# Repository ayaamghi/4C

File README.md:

<div align="center">

# 4C

</div>

Four-channel brushed DC motor controller board built around an STM32G4, DRV8701 gate drivers, and discrete MOSFET bridges.

## Layout

- `hardware/kicad/4C.kicad_pro` - open this in KiCad
- `hardware/kicad/libs/` - project-local imported parts and 3D models
- `firmware/cubemx/` - STM32CubeMX config
- `docs/datasheets/` - datasheets and layout notes

Hardware is still in progress; check the schematic, BOM, and fab outputs before ordering.

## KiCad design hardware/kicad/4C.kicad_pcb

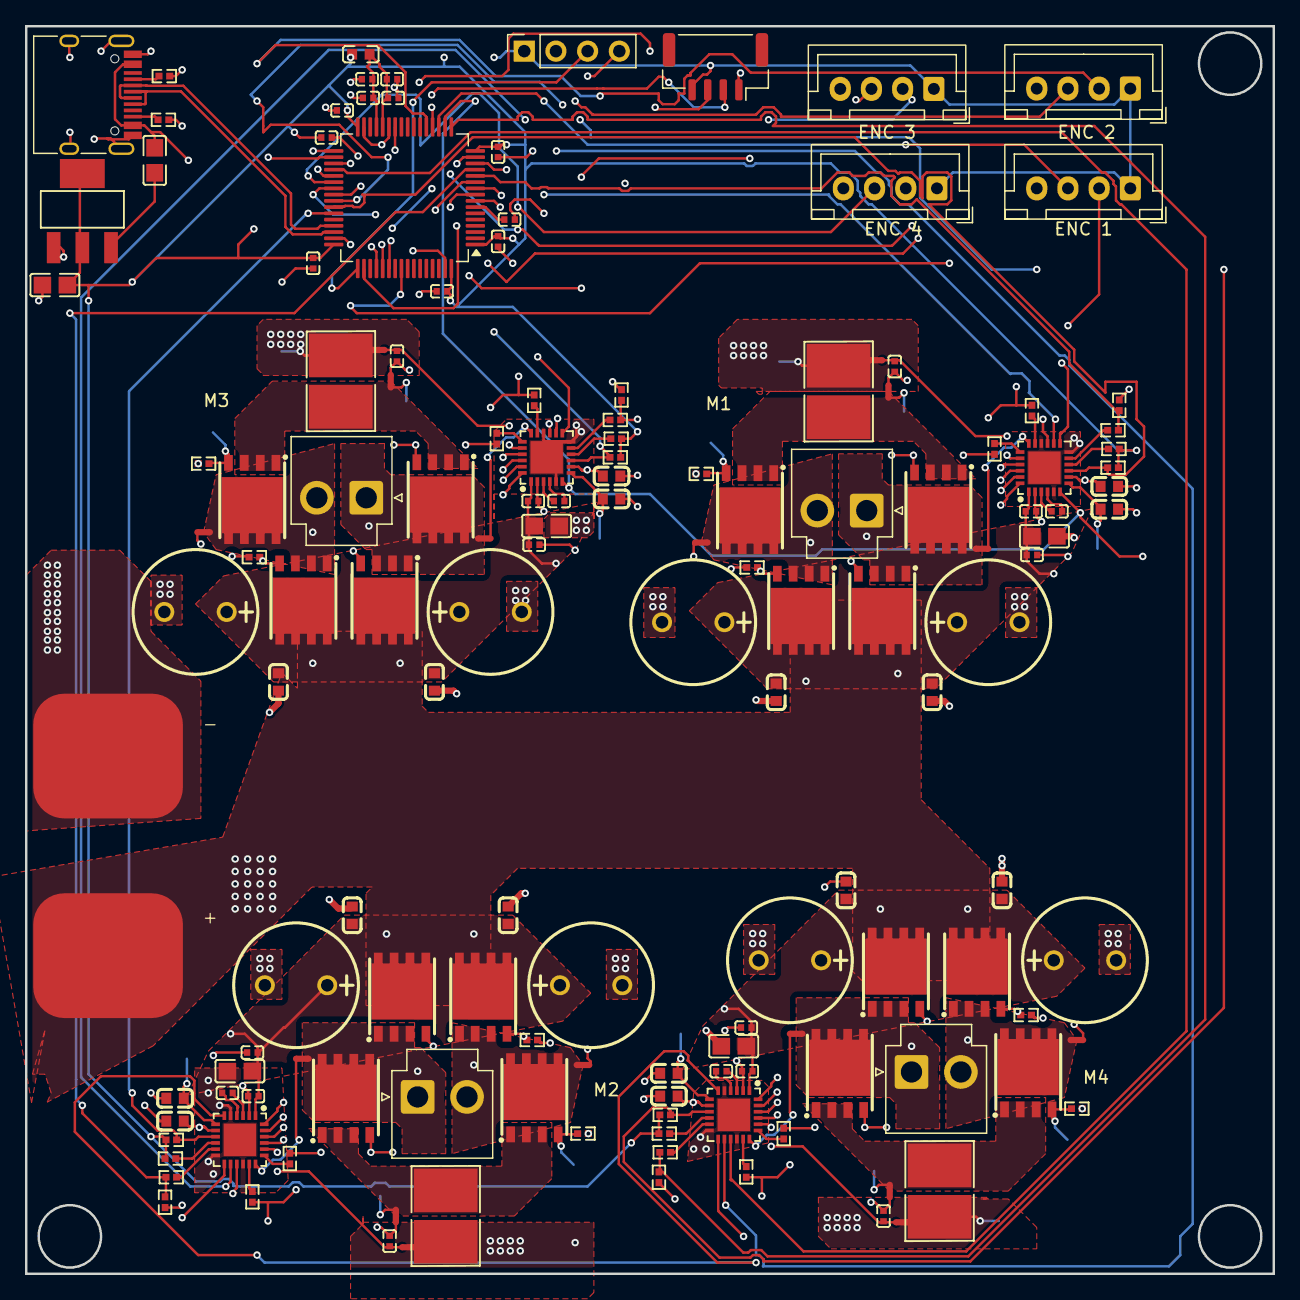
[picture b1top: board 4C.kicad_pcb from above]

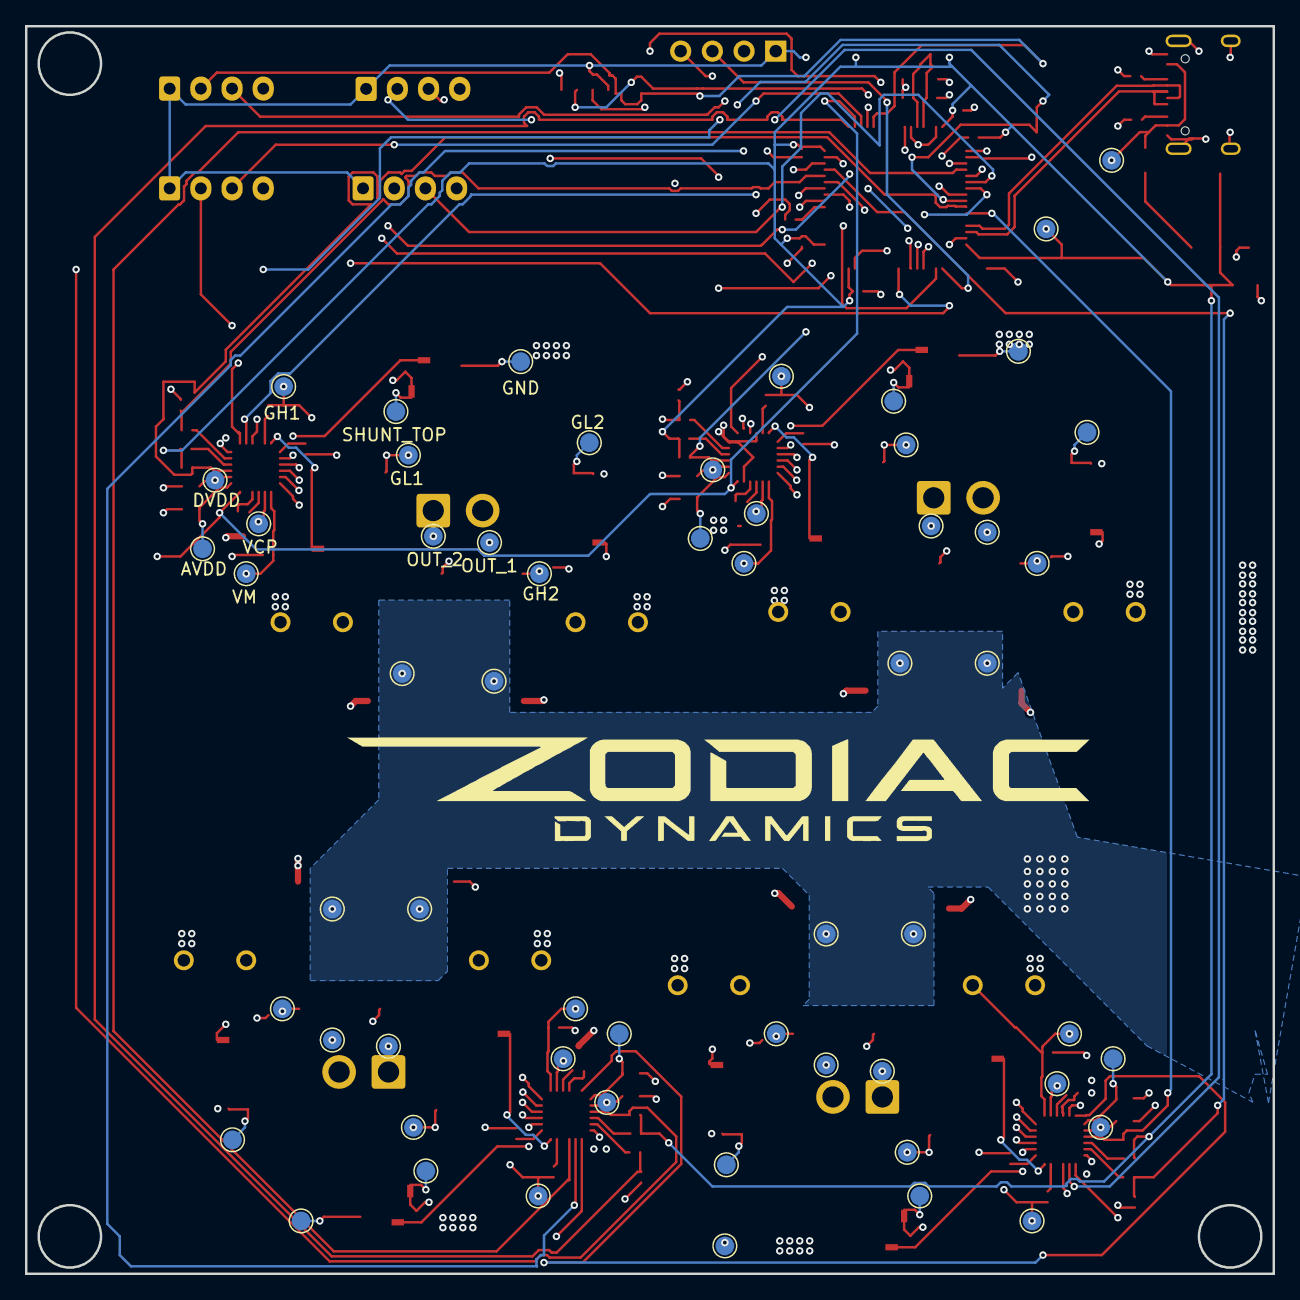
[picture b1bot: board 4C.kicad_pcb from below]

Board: 4 copper layers, 100.0 x 100.0 mm, 204 parts (58 on the bottom side), 129 nets.

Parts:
C1, C16, C31, C46: GRM32ER71H106KA12L; C0805
C2, C6, C17, C21, C32, C36, C47, C51, C62, C64, C66, C67, C68, C69, C72, C73: C1608X7R1H104K; C0402
C3, C4, C7, C14, C18, C19, C22, C29, C33, C34, C37, C44, C48, C49, C52, C59: GRM188R70J105KA01D; C0603
C5, C20, C35, C50, C61, C63: CL05A105KA5NQNC; C0402
C8, C15, C23, C30, C38, C45, C53, C60: ECA-1HM471; CAP-TH_BD10.0-P5.00-D0.6-FD
C9, C24, C39, C54: GRM155R71C102KA01D; C0402
C65: GRM32ER71H106KA12L; C0402
C70: 10uF; C0805
C71: 22uF; C0805
J1: Conn_01x04; PinSocket_1x04_P2.54mm_Vertical
J2: Conn_01x02; SolderWirePad_2x01_SMD_10x12mm
J10, J11, J12, J13: Conn_01x02; JST_VH_B2P-VH_1x02_P3.96mm_Vertical
J18, J19, J20, J21: Conn_01x04; JST_XH_B4B-XH-A_1x04_P2.50mm_Vertical
J22: Conn_01x04; JST_GH_SM04B-GHS-TB_1x04-1MP_P1.25mm_Horizontal
J25: USB_C_Receptacle_USB2.0_16P; USB_C_Receptacle_HRO_TYPE-C-31-M-12
L1: GZ1608D601TF; L0603
NT1, NT2, NT3, NT4, NT5, NT6, NT7, NT8, NT9, NT10, NT11, NT12, NT13, NT14, NT15, NT16: Net-Tie; NetTie-2_SMD_Pad0.5mm
Q1, Q2, Q3, Q4, Q5, Q6, Q7, Q8, Q9, Q10, Q11, Q12, Q13, Q14, Q15, Q16: CSD18540Q5B; VSON-CLIP-8_L5.0-W6.0-P1.27-BL
R1, R2, R4, R12, R13, R15, R23, R24, R26, R34, R35, R37: CRCW060310K0JNEA; R0402
R3, R14, R25, R36: CRCW06037K50JNEA; R0402
R7, R8, R10, R11, R18, R19, R21, R22, R29, R30, R32, R33, R40, R41, R43, R44, R45, R46: CRCW06030000Z0EA; R0402
R9, R20, R31, R42: CRA2512-FZ-R010ELF; R2818
TP1, TP2, TP15, TP16, TP29, TP30, TP43, TP44: VM; TestPoint_Pad_D1.5mm
TP3, TP4, TP5, TP6, TP7, TP8, TP9, TP10, TP11, TP12, TP13, TP14, TP17, TP18, TP19, TP20, TP21, TP22, TP23, TP24, TP25, TP26, TP27, TP28, TP31, TP32, TP33, TP34, TP35, TP36, TP37, TP38, TP39, TP40, TP41, TP42, TP45, TP46, TP47, TP48, TP49, TP50, TP51, TP52, TP53, TP54, TP55, TP56: AVDD; TestPoint_Pad_D1.5mm
TP57, TP58: TestPoint; TestPoint_Pad_D1.5mm
U1, U2, U3, U4: DRV8701ERGER; VQFN-24_L4.0-W4.0-P0.50-BL-EP2.5
U5: STM32G474RETx; LQFP-64_10x10mm_P0.5mm
U6: AMS1117-3.3; SOT-223-3_L6.5-W3.4-P2.30-LS7.0-BR

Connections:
+3.3V: C65.1, C66.1, C67.1, C68.1, C69.1, C71.1, C73.1, J1.1, J18.1, J19.1, J20.1, J21.1, J22.4, L1.1, R1.1, R2.1, R12.1, R13.1, R23.1, R24.1, R34.1, R35.1, TP58.1, U5.1 (VBAT), U5.16 (VDD), U5.32 (VDD), U5.48 (VDD), U5.64 (VDD), U6.2 (VOUT), U6.4 (VOUT)
+5V: C70.2, J25.A4 (VBUS), J25.A9 (VBUS), J25.B4 (VBUS), J25.B9 (VBUS), TP57.1
/D+: J25.A6 (D+), J25.B6 (D+), U5.46 (PA12)
/D-: J25.A7 (D-), J25.B7 (D-), U5.45 (PA11)
/ENC_1_A: J18.3, U5.19 (PA5)
/ENC_1_B: J18.2, U5.56 (PB3)
/ENC_2_A: J19.3, U5.20 (PA6)
/ENC_2_B: J19.2, U5.21 (PA7)
/ENC_3_A: J20.3, U5.26 (PB2)
/ENC_3_B: J20.2, U5.54 (PC12)
/ENC_4_A: J21.3, U5.38 (PC6)
/ENC_4_B: J21.2, U5.39 (PC7)
/EN_1: U1.14 (EN/IN2), U5.8 (PC0)
/EN_2: U2.14 (EN/IN2), U5.9 (PC1)
/EN_3: U3.14 (EN/IN2), U5.10 (PC2)
/EN_4: U4.14 (EN/IN2), U5.11 (PC3)
/PH_DIR_1: U1.15 (PH/IN1), U5.33 (PB11)
/PH_DIR_2: U2.15 (PH/IN1), U5.34 (PB12)
/PH_DIR_3: U3.15 (PH/IN1), U5.35 (PB13)
/PH_DIR_4: U4.15 (PH/IN1), U5.36 (PB14)
/SO_1: R3.1, R4.1, U5.12 (PA0)
/SO_2: R14.1, R15.1, U5.13 (PA1)
/SO_3: R25.1, R26.1, U5.14 (PA2)
/SO_4: R36.1, R37.1, U5.17 (PA3)
/UART_RX: J22.2, U5.53 (PC11)
/UART_TX: J22.3, U5.52 (PC10)
/VREF: U1.6 (VREF), U2.6 (VREF), U3.6 (VREF), U4.6 (VREF), U5.18 (PA4)
/drh1/AVDD: C3.1, TP3.1, U1.7 (AVDD)
/drh1/DVDD: C4.2, TP4.1, U1.8 (DVDD)
/drh1/GH1: R10.1, U1.17 (GH1)
/drh1/GH2: R7.2, U1.24 (GH2)
/drh1/GL1: R11.1, U1.19 (GL1)
/drh1/GL2: R8.2, U1.22 (GL2)
/drh1/OUT1: J10.2, NT1.2, Q1.1 (S), Q1.2 (S), Q1.3 (S), Q2.5 (D), Q2.6 (D), Q2.7 (D), Q2.8 (D), TP8.1
/drh1/OUT2: J10.1, NT4.2, Q3.1 (S), Q3.2 (S), Q3.3 (S), Q4.5 (D), Q4.6 (D), Q4.7 (D), Q4.8 (D), TP10.1
/drh1/SH1: NT4.1, U1.18 (SH1)
/drh1/SH2: NT1.1, U1.23 (SH2)
/drh1/SHUNT_TOP: NT2.1, Q2.1 (S), Q2.2 (S), Q2.3 (S), Q4.1 (S), Q4.2 (S), Q4.3 (S), R9.2, TP9.1
/drh1/SNSOUT: R1.2, U1.10 (SNSOUT)
/drh1/S_N: C9.2, NT3.2, U1.20 (SN)
/drh1/S_P: C9.1, NT2.2, U1.21 (SP)
/drh1/VCP: C5.1, TP2.1, U1.2 (VCP)
/drh2/AVDD: C18.1, TP17.1, U2.7 (AVDD)
/drh2/DVDD: C19.2, TP18.1, U2.8 (DVDD)
/drh2/GH1: R21.1, U2.17 (GH1)
/drh2/GH2: R18.2, U2.24 (GH2)
/drh2/GL1: R22.1, U2.19 (GL1)
/drh2/GL2: R19.2, U2.22 (GL2)
/drh2/OUT1: J11.2, NT5.2, Q5.1 (S), Q5.2 (S), Q5.3 (S), Q6.5 (D), Q6.6 (D), Q6.7 (D), Q6.8 (D), TP22.1
/drh2/OUT2: J11.1, NT8.2, Q7.1 (S), Q7.2 (S), Q7.3 (S), Q8.5 (D), Q8.6 (D), Q8.7 (D), Q8.8 (D), TP24.1
/drh2/SH1: NT8.1, U2.18 (SH1)
/drh2/SH2: NT5.1, U2.23 (SH2)
/drh2/SHUNT_TOP: NT6.1, Q6.1 (S), Q6.2 (S), Q6.3 (S), Q8.1 (S), Q8.2 (S), Q8.3 (S), R20.2, TP23.1
/drh2/SNSOUT: R12.2, U2.10 (SNSOUT)
/drh2/S_N: C24.2, NT7.2, U2.20 (SN)
/drh2/S_P: C24.1, NT6.2, U2.21 (SP)
/drh2/VCP: C20.1, TP16.1, U2.2 (VCP)
/drh3/AVDD: C33.1, TP31.1, U3.7 (AVDD)
/drh3/DVDD: C34.2, TP32.1, U3.8 (DVDD)
/drh3/GH1: R32.1, U3.17 (GH1)
/drh3/GH2: R29.2, U3.24 (GH2)
/drh3/GL1: R33.1, U3.19 (GL1)
/drh3/GL2: R30.2, U3.22 (GL2)
/drh3/OUT1: J12.2, NT9.2, Q9.1 (S), Q9.2 (S), Q9.3 (S), Q10.5 (D), Q10.6 (D), Q10.7 (D), Q10.8 (D), TP36.1
/drh3/OUT2: J12.1, NT12.2, Q11.1 (S), Q11.2 (S), Q11.3 (S), Q12.5 (D), Q12.6 (D), Q12.7 (D), Q12.8 (D), TP38.1
/drh3/SH1: NT12.1, U3.18 (SH1)
/drh3/SH2: NT9.1, U3.23 (SH2)
/drh3/SHUNT_TOP: NT10.1, Q10.1 (S), Q10.2 (S), Q10.3 (S), Q12.1 (S), Q12.2 (S), Q12.3 (S), R31.2, TP37.1
/drh3/SNSOUT: R23.2, U3.10 (SNSOUT)
/drh3/S_N: C39.2, NT11.2, U3.20 (SN)
/drh3/S_P: C39.1, NT10.2, U3.21 (SP)
/drh3/VCP: C35.1, TP30.1, U3.2 (VCP)
/drh4/AVDD: C48.1, TP45.1, U4.7 (AVDD)
/drh4/DVDD: C49.2, TP46.1, U4.8 (DVDD)
/drh4/GH1: R43.1, U4.17 (GH1)
/drh4/GH2: R40.2, U4.24 (GH2)
/drh4/GL1: R44.1, U4.19 (GL1)
/drh4/GL2: R41.2, U4.22 (GL2)
/drh4/OUT1: J13.2, NT13.2, Q13.1 (S), Q13.2 (S), Q13.3 (S), Q14.5 (D), Q14.6 (D), Q14.7 (D), Q14.8 (D), TP50.1
/drh4/OUT2: J13.1, NT16.2, Q15.1 (S), Q15.2 (S), Q15.3 (S), Q16.5 (D), Q16.6 (D), Q16.7 (D), Q16.8 (D), TP52.1
/drh4/SH1: NT16.1, U4.18 (SH1)
/drh4/SH2: NT13.1, U4.23 (SH2)
/drh4/SHUNT_TOP: NT14.1, Q14.1 (S), Q14.2 (S), Q14.3 (S), Q16.1 (S), Q16.2 (S), Q16.3 (S), R42.2, TP51.1
/drh4/SNSOUT: R34.2, U4.10 (SNSOUT)
/drh4/S_N: C54.2, NT15.2, U4.20 (SN)
/drh4/S_P: C54.1, NT14.2, U4.21 (SP)
/drh4/VCP: C50.1, TP44.1, U4.2 (VCP)
/nFAULT_1: R2.2, U1.9 (FAULT), U5.42 (PA8)
/nFAULT_2: R13.2, U2.9 (FAULT), U5.43 (PA9)
/nFAULT_3: R24.2, U3.9 (FAULT), U5.40 (PC8)
/nFAULT_4: R35.2, U4.9 (FAULT), U5.41 (PC9)
/nSLEEP: U1.13 (SLEEP), U2.13 (SLEEP), U3.13 (SLEEP), U4.13 (SLEEP), U5.37 (PB15)
GND: C1.2, C2.2, C3.2, C4.1, C7.1, C8.2 (-), C14.1, C15.2 (-), C16.2, C17.2, C18.2, C19.1, C22.1, C23.2 (-), C29.1, C30.2 (-), C31.2, C32.2, C33.2, C34.1, C37.1, C38.2 (-), C44.1, C45.2 (-), C46.2, C47.2, C48.2, C49.1, C52.1, C53.2 (-), C59.1, C60.2 (-), C61.1, C62.2, C63.1, C64.2, C65.2, C66.2, C67.2, C68.2, C69.2, C71.2, C72.2, C73.2, J1.2, J2.1, J18.4, J19.4, J20.4, J21.4, J22.1, J25.A1 (GND), J25.A12 (GND), J25.B1 (GND), J25.B12 (GND), J25.S1 (SHIELD), NT3.1, NT7.1, NT11.1, NT15.1, R4.2, R9.1, R15.2, R20.1, R26.2, R31.1, R37.2, R42.1, R45.2, R46.2, TP11.1, TP25.1, TP39.1, TP53.1, U1.5 (GND), U1.12 (IDRIVE), U1.16 (GND), U1.25 (PAD), U2.5 (GND), U2.12 (IDRIVE), U2.16 (GND), U2.25 (PAD), U3.5 (GND), U3.12 (IDRIVE), U3.16 (GND), U3.25 (PAD), U4.5 (GND), U4.12 (IDRIVE), U4.16 (GND), U4.25 (PAD), U5.15 (VSS), U5.27 (VSSA), U5.31 (VSS), U5.47 (VSS), U5.63 (VSS), U6.1 (GND)
unnamed: J1.3, U5.49 (PA13)
unnamed: J1.4, U5.50 (PA14)
unnamed: J25.A5 (CC1), R45.1
unnamed: J25.B5 (CC2), R46.1
unnamed: Q1.4 (G), R7.1, TP5.1
unnamed: Q2.4 (G), R8.1, TP6.1
unnamed: Q3.4 (G), R10.2, TP13.1
unnamed: Q4.4 (G), R11.2, TP14.1
unnamed: Q5.4 (G), R18.1, TP19.1
unnamed: Q6.4 (G), R19.1, TP20.1
unnamed: Q7.4 (G), R21.2, TP27.1
unnamed: Q8.4 (G), R22.2, TP28.1
unnamed: Q9.4 (G), R29.1, TP33.1
unnamed: Q10.4 (G), R30.1, TP34.1
unnamed: Q11.4 (G), R32.2, TP41.1
unnamed: Q12.4 (G), R33.2, TP42.1
unnamed: Q13.4 (G), R40.1, TP47.1
unnamed: Q14.4 (G), R41.1, TP48.1
unnamed: Q15.4 (G), R43.2, TP55.1
unnamed: Q16.4 (G), R44.2, TP56.1
unnamed: C6.1, U1.3 (CPH)
unnamed: C6.2, U1.4 (CPL)
unnamed: R3.2, U1.11 (SO)
unnamed: C21.1, U2.3 (CPH)
unnamed: C21.2, U2.4 (CPL)
unnamed: R14.2, U2.11 (SO)
unnamed: C36.1, U3.3 (CPH)
unnamed: C36.2, U3.4 (CPL)
unnamed: R25.2, U3.11 (SO)
unnamed: C51.1, U4.3 (CPH)
unnamed: C51.2, U4.4 (CPL)
unnamed: R36.2, U4.11 (SO)
unnamed: C72.1, U5.7 (PG10)
unnamed: C70.1, U6.3 (VIN)
VDDA: C61.2, C62.1, C63.2, C64.1, L1.2, U5.28 (VREF+), U5.29 (VDDA)
VM: C1.1, C2.1, C5.2, C7.2, C8.1 (+), C14.2, C15.1 (+), C16.1, C17.1, C20.2, C22.2, C23.1 (+), C29.2, C30.1 (+), C31.1, C32.1, C35.2, C37.2, C38.1 (+), C44.2, C45.1 (+), C46.1, C47.1, C50.2, C52.2, C53.1 (+), C59.2, C60.1 (+), J2.2, Q1.5 (D), Q1.6 (D), Q1.7 (D), Q1.8 (D), Q3.5 (D), Q3.6 (D), Q3.7 (D), Q3.8 (D), Q5.5 (D), Q5.6 (D), Q5.7 (D), Q5.8 (D), Q7.5 (D), Q7.6 (D), Q7.7 (D), Q7.8 (D), Q9.5 (D), Q9.6 (D), Q9.7 (D), Q9.8 (D), Q11.5 (D), Q11.6 (D), Q11.7 (D), Q11.8 (D), Q13.5 (D), Q13.6 (D), Q13.7 (D), Q13.8 (D), Q15.5 (D), Q15.6 (D), Q15.7 (D), Q15.8 (D), TP1.1, TP7.1, TP12.1, TP15.1, TP21.1, TP26.1, TP29.1, TP35.1, TP40.1, TP43.1, TP49.1, TP54.1, U1.1 (VM), U2.1 (VM), U3.1 (VM), U4.1 (VM)

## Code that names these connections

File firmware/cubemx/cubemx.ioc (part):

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Mcu.Name=STM32G474R(B-C-E)Tx
Mcu.Package=LQFP64
Mcu.UserName=STM32G474RETx
PA0.GPIOParameters=GPIO_Label
PA0.GPIO_Label=SO_1
PA0.Mode=IN1-Single-Ended
PA0.Signal=ADC1_IN1
PA1.GPIOParameters=GPIO_Label
PA1.GPIO_Label=SO_2
PA1.Mode=IN2-Single-Ended
PA1.Signal=ADC1_IN2
PA10.GPIOParameters=GPIO_Label
PA10.GPIO_Label=PWM_1
PA10.Signal=S_TIM2_CH4
PA11.Mode=Device
PA11.Signal=USB_DM
PA12.Mode=Device
PA12.Signal=USB_DP
PA13.Mode=Serial_Wire
PA13.Signal=SYS_JTMS-SWDIO
PA14.Mode=Serial_Wire
PA14.Signal=SYS_JTCK-SWCLK
PA15.Mode=I2C
PA15.Signal=I2C1_SCL
PA2.GPIOParameters=GPIO_Label
PA2.GPIO_Label=SO_3
PA2.Mode=IN3-Single-Ended
PA2.Signal=ADC1_IN3
PA3.GPIOParameters=GPIO_Label
PA3.GPIO_Label=SO_4
PA3.Mode=IN4-Single-Ended
PA3.Signal=ADC1_IN4
PA4.Signal=COMP_DAC11_group
PA5.GPIOParameters=GPIO_Label
PA5.GPIO_Label=ENC_1_A
PA5.Signal=S_TIM2_CH1
PA6.GPIOParameters=GPIO_Label
PA6.GPIO_Label=ENC_2_A
PA6.Signal=S_TIM3_CH1
PA7.GPIOParameters=GPIO_Label
PA7.GPIO_Label=ENC_2_B
PA7.Signal=S_TIM3_CH2
PA8.GPIOParameters=GPIO_PuPd,GPIO_Label
PA8.GPIO_Label=nFAULT_1
PA8.GPIO_PuPd=GPIO_PULLUP
PA8.Signal=GPIO_Input
PA9.GPIOParameters=GPIO_PuPd,GPIO_Label
PA9.GPIO_Label=nFAULT_2
PA9.GPIO_PuPd=GPIO_PULLUP
PA9.Signal=GPIO_Input
PB0.GPIOParameters=GPIO_Label
PB0.GPIO_Label=PWM_3
PB0.Signal=S_TIM3_CH3
PB1.GPIOParameters=GPIO_Label
PB1.GPIO_Label=PWM_4
PB1.Signal=S_TIM3_CH4
PB10.GPIOParameters=GPIO_Label
PB10.GPIO_Label=PWM_2
PB10.Signal=S_TIM2_CH3
PB11.GPIOParameters=GPIO_Label
PB11.GPIO_Label=PH_DIR_1
PB11.Signal=GPIO_Output
PB12.GPIOParameters=GPIO_Label
PB12.GPIO_Label=PH_DIR_2
PB12.Signal=GPIO_Output
PB13.GPIOParameters=GPIO_Label
PB13.GPIO_Label=PH_DIR_3
PB13.Signal=GPIO_Output
PB14.GPIOParameters=GPIO_Label
PB14.GPIO_Label=PH_DIR_4
PB14.Signal=GPIO_Output
PB15.GPIOParameters=GPIO_Label
PB15.GPIO_Label=nSLEEP
PB15.Signal=GPIO_Output
PB2.GPIOParameters=GPIO_Label
PB2.GPIO_Label=ENC_3_A
PB2.Signal=S_TIM5_CH1
PB3.GPIOParameters=GPIO_Label
PB3.GPIO_Label=ENC_1_B
PB3.Signal=S_TIM2_CH2
PB6.GPIOParameters=GPIO_Label
PB6.GPIO_Label=PWM_5
PB6.Signal=S_TIM4_CH1
PB7.Mode=I2C
PB7.Signal=I2C1_SDA
PB8-BOOT0.Mode=FDCAN_Activate
PB8-BOOT0.Signal=FDCAN1_RX
PB9.Mode=FDCAN_Activate
PB9.Signal=FDCAN1_TX
PC0.GPIOParameters=GPIO_Label
PC0.GPIO_Label=EN_1
PC0.Signal=S_TIM1_CH1
PC1.GPIOParameters=GPIO_Label
PC1.GPIO_Label=EN_2
PC1.Signal=S_TIM1_CH2
PC10.Mode=Asynchronous
PC10.Signal=UART4_TX
PC11.Mode=Asynchronous
PC11.Signal=UART4_RX
PC12.GPIOParameters=GPIO_Label
PC12.GPIO_Label=ENC_3_B
PC12.Signal=S_TIM5_CH2
PC2.GPIOParameters=GPIO_Label
PC2.GPIO_Label=EN_3
PC2.Signal=S_TIM1_CH3
PC3.GPIOParameters=GPIO_Label
PC3.GPIO_Label=EN_4
PC3.Signal=S_TIM1_CH4
PC6.GPIOParameters=GPIO_Label
PC6.GPIO_Label=ENC_4_A
PC6.Signal=S_TIM8_CH1
PC7.GPIOParameters=GPIO_Label
PC7.GPIO_Label=ENC_4_B
PC7.Signal=S_TIM8_CH2
PC8.GPIOParameters=GPIO_PuPd,GPIO_Label
PC8.GPIO_Label=nFAULT_3
PC8.GPIO_PuPd=GPIO_PULLUP
PC8.Signal=GPIO_Input
PC9.GPIOParameters=GPIO_PuPd,GPIO_Label
PC9.GPIO_Label=nFAULT_4
PC9.GPIO_PuPd=GPIO_PULLUP
PC9.Signal=GPIO_Input
RCC.HSE_VALUE=8000000
RCC.SYSCLKFreq_VALUE=170000000
RCC.SYSCLKSource=RCC_SYSCLKSOURCE_PLLCLK
board=custom

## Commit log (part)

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2026-04-04 completed copying TI ref diagram
2026-04-05 pre-STM32 signal routing
2026-06-25 checkpoints
